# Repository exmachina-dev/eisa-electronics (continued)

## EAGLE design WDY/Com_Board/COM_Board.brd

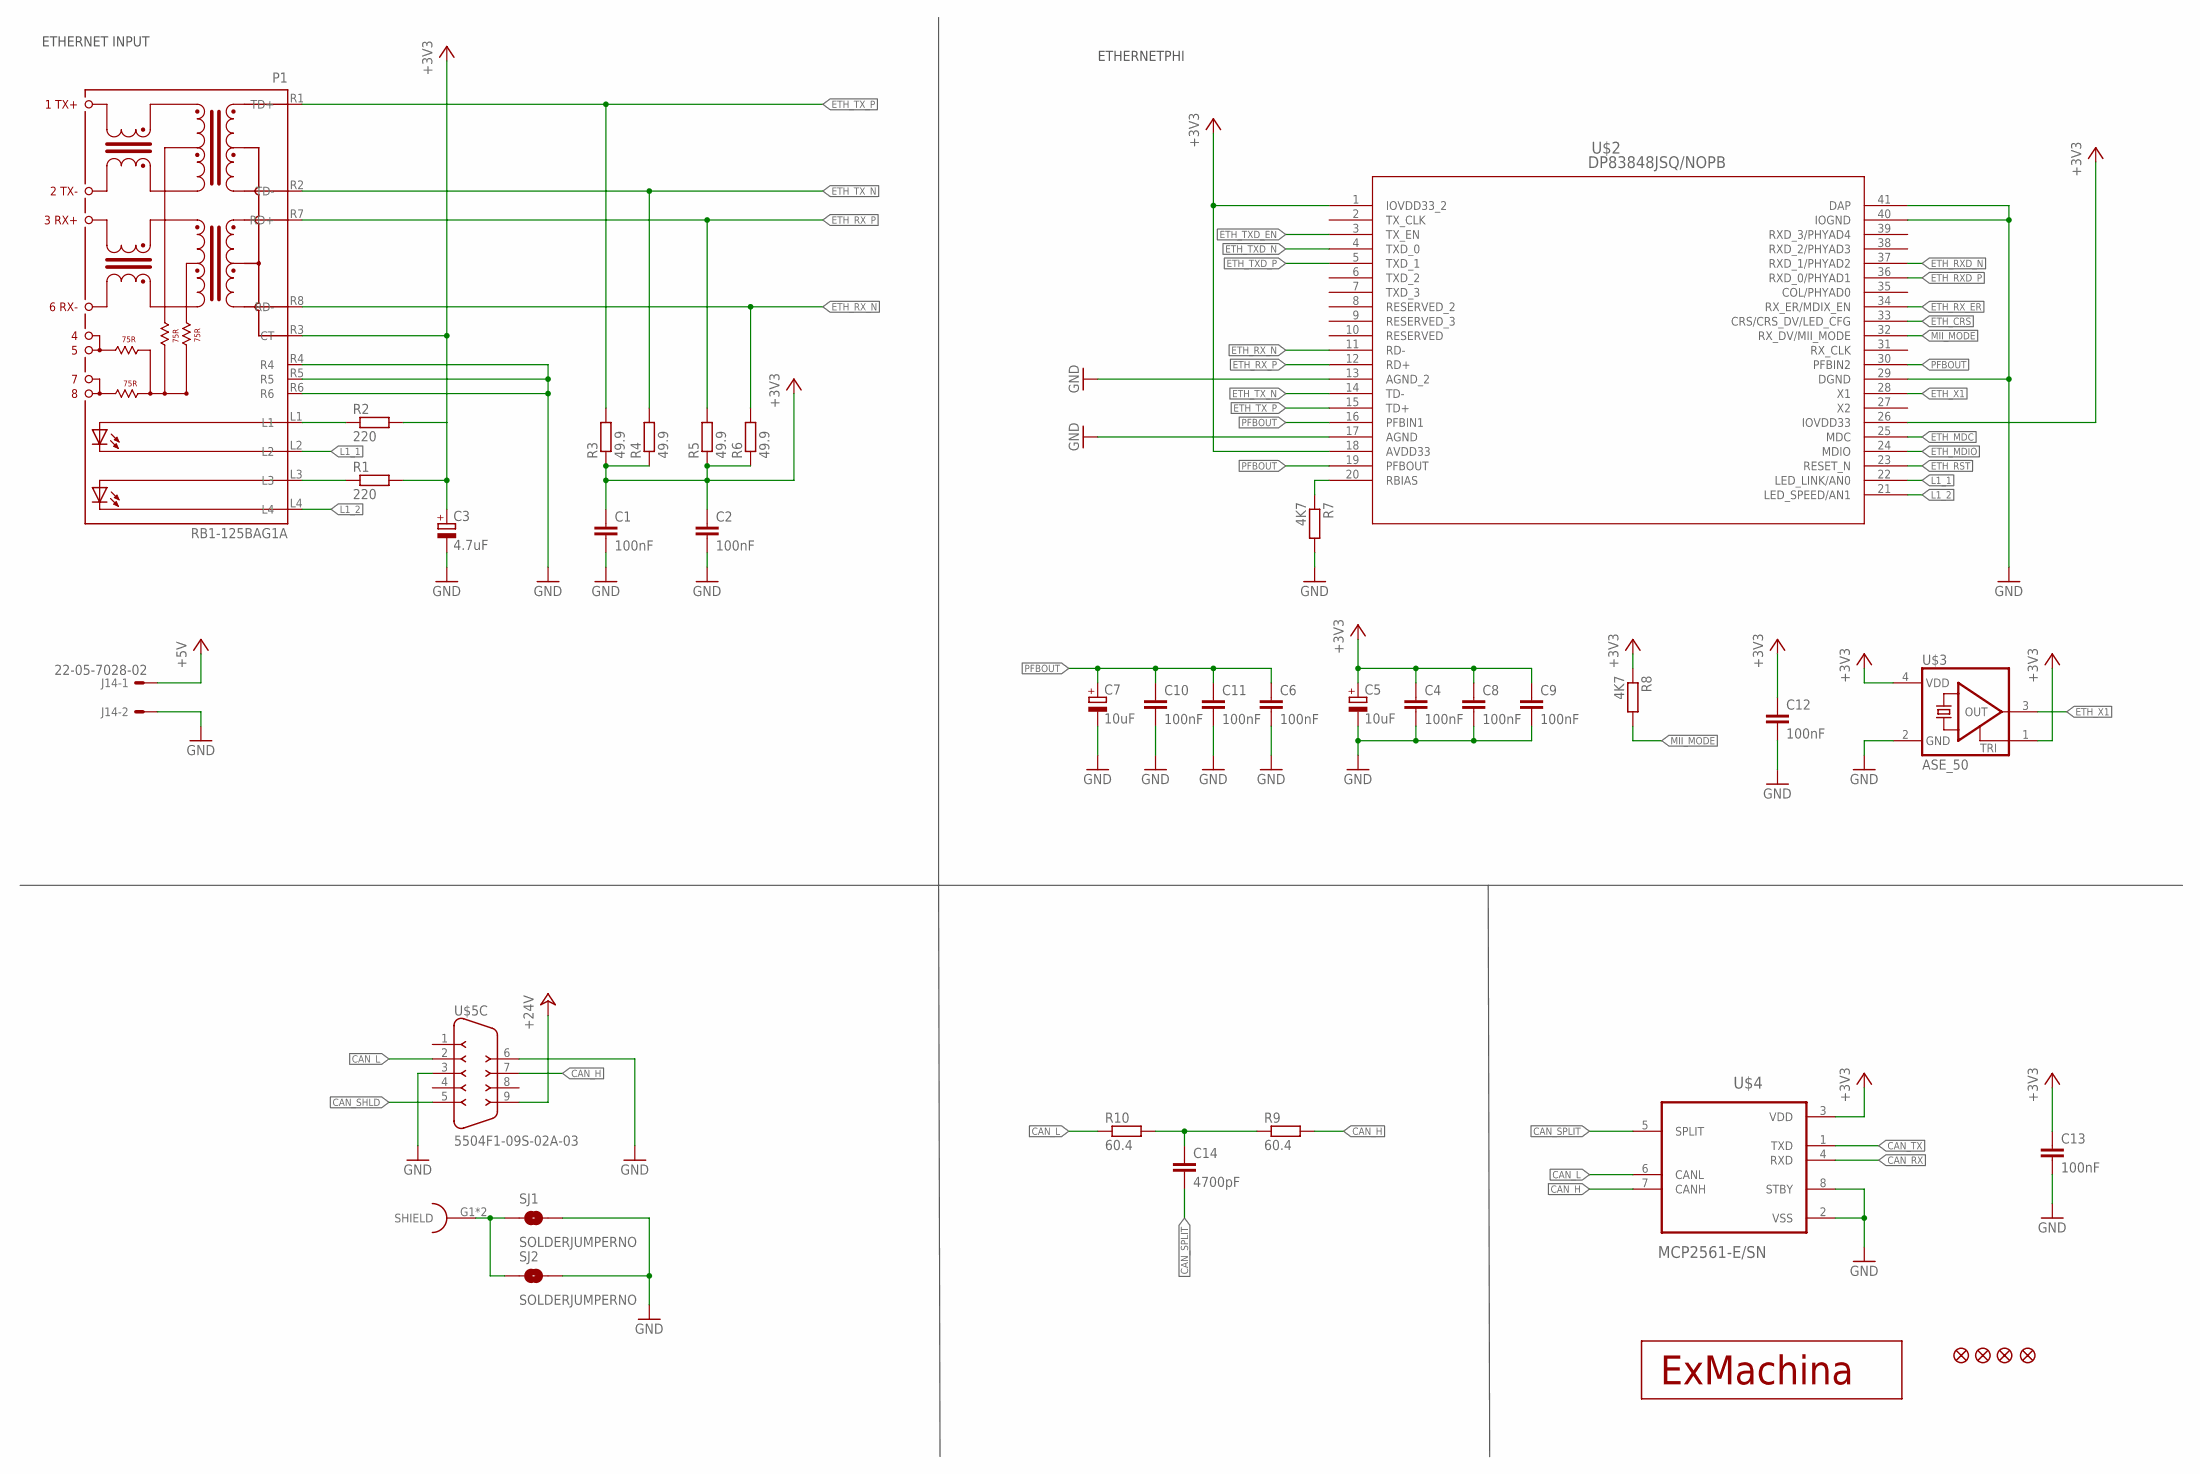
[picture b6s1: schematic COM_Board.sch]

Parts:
C1, C2, C4, C6, C8, C9, C10, C11, C12, C13: 100nF; C0603
C3: 4.7uF; CT3216
C5, C7: 10uF; CT3216
C14: 4700pF; C0603
J14: 22-05-7028-02; 7395-02
JP2, JP3, JP4, JP5: FIDUCIAL1X2; FIDUCIAL-1X2
P1: RB1-125BAG1A; WIZNET_RB1-125BAG1A
R1, R2: 220; R0603
R3, R4, R5, R6: 49.9; R0603
R7, R8: 4K7; R0603
R9, R10: 60.4; R0603
SJ1, SJ2: SOLDERJUMPERNO; SJ_2S-NO
U$1: EXMACHINA-LOGO-NAME; EXM-LOGO-BASELINE
U$2: DP83848JSQ/NOPB; SQA40B
U$3: ASE_50; ASE
U$4: MCP2561-E/SN; SOIC127P600X175-8N
U$5: 5504F1-09S-02A-03; 5504F1-09S-02A

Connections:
+3V3: C1.1, C2.1, C3.+, C4.1, C5.+, C8.1, C9.1, C12.1, C13.1, P1.R3 (CT), R1.2, R2.2, R3.1, R4.1, R5.1, R6.1, R8.1, U$2.1 (IOVDD33_2), U$2.18 (AVDD33), U$2.26 (IOVDD33), U$3.1 (TRI), U$3.4 (VDD), U$4.3 (VDD)
+5V: J14.1
+24V: U$5.9
CAN_H: R9.2, U$4.7 (CANH), U$5.7
CAN_L: R10.1, U$4.6 (CANL), U$5.2
CAN_RX: U$4.4 (RXD)
CAN_SHLD: U$5.5
CAN_SPLIT: C14.2, U$4.5 (SPLIT)
CAN_TX: U$4.1 (TXD)
ETH_CRS: U$2.33 (CRS/CRS_DV/LED_CFG)
ETH_MDC: U$2.25 (MDC)
ETH_MDIO: U$2.24 (MDIO)
ETH_RST: U$2.23 (RESET_N)
ETH_RXD_N: U$2.37 (RXD_1/PHYAD2)
ETH_RXD_P: U$2.36 (RXD_0/PHYAD1)
ETH_RX_ER: U$2.34 (RX_ER/MDIX_EN)
ETH_RX_N: P1.R8 (RD-), R6.2, U$2.11 (RD-)
ETH_RX_P: P1.R7 (RD+), R5.2, U$2.12 (RD+)
ETH_TXD_EN: U$2.3 (TX_EN)
ETH_TXD_N: U$2.4 (TXD_0)
ETH_TXD_P: U$2.5 (TXD_1)
ETH_TX_N: P1.R2 (TD-), R4.2, U$2.14 (TD-)
ETH_TX_P: P1.R1 (TD+), R3.2, U$2.15 (TD+)
ETH_X1: U$2.28 (X1), U$3.3 (OUT)
GND: C1.2, C2.2, C3.-, C4.2, C5.-, C6.2, C7.-, C8.2, C9.2, C10.2, C11.2, C12.2, C13.2, J14.2, P1.R4, P1.R5, P1.R6, R7.2, SJ1.2, SJ2.2, U$2.13 (AGND_2), U$2.17 (AGND), U$2.29 (DGND), U$2.40 (IOGND), U$2.41 (DAP), U$3.2 (GND), U$4.2 (VSS), U$4.8 (STBY), U$5.3, U$5.6
L1_1: P1.L2, U$2.22 (LED_LINK/AN0)
L1_2: P1.L4, U$2.21 (LED_SPEED/AN1)
MII_MODE: R8.2, U$2.32 (RX_DV/MII_MODE)
unnamed: C14.1, R9.1, R10.2
unnamed: R7.1, U$2.20 (RBIAS)
unnamed: SJ1.1, SJ2.1, U$5.G1 (SHIELD), U$5.G2 (SHIELD)
unnamed: P1.L1, R2.1
unnamed: P1.L3, R1.1
PFBOUT: C6.1, C7.+, C10.1, C11.1, U$2.16 (PFBIN1), U$2.19 (PFBOUT), U$2.30 (PFBIN2)

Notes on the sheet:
ETHERNET INPUT
ETHERNETPHI

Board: 2 copper layers, 37 parts (0 on the bottom side), 19 nets, no tracks yet.

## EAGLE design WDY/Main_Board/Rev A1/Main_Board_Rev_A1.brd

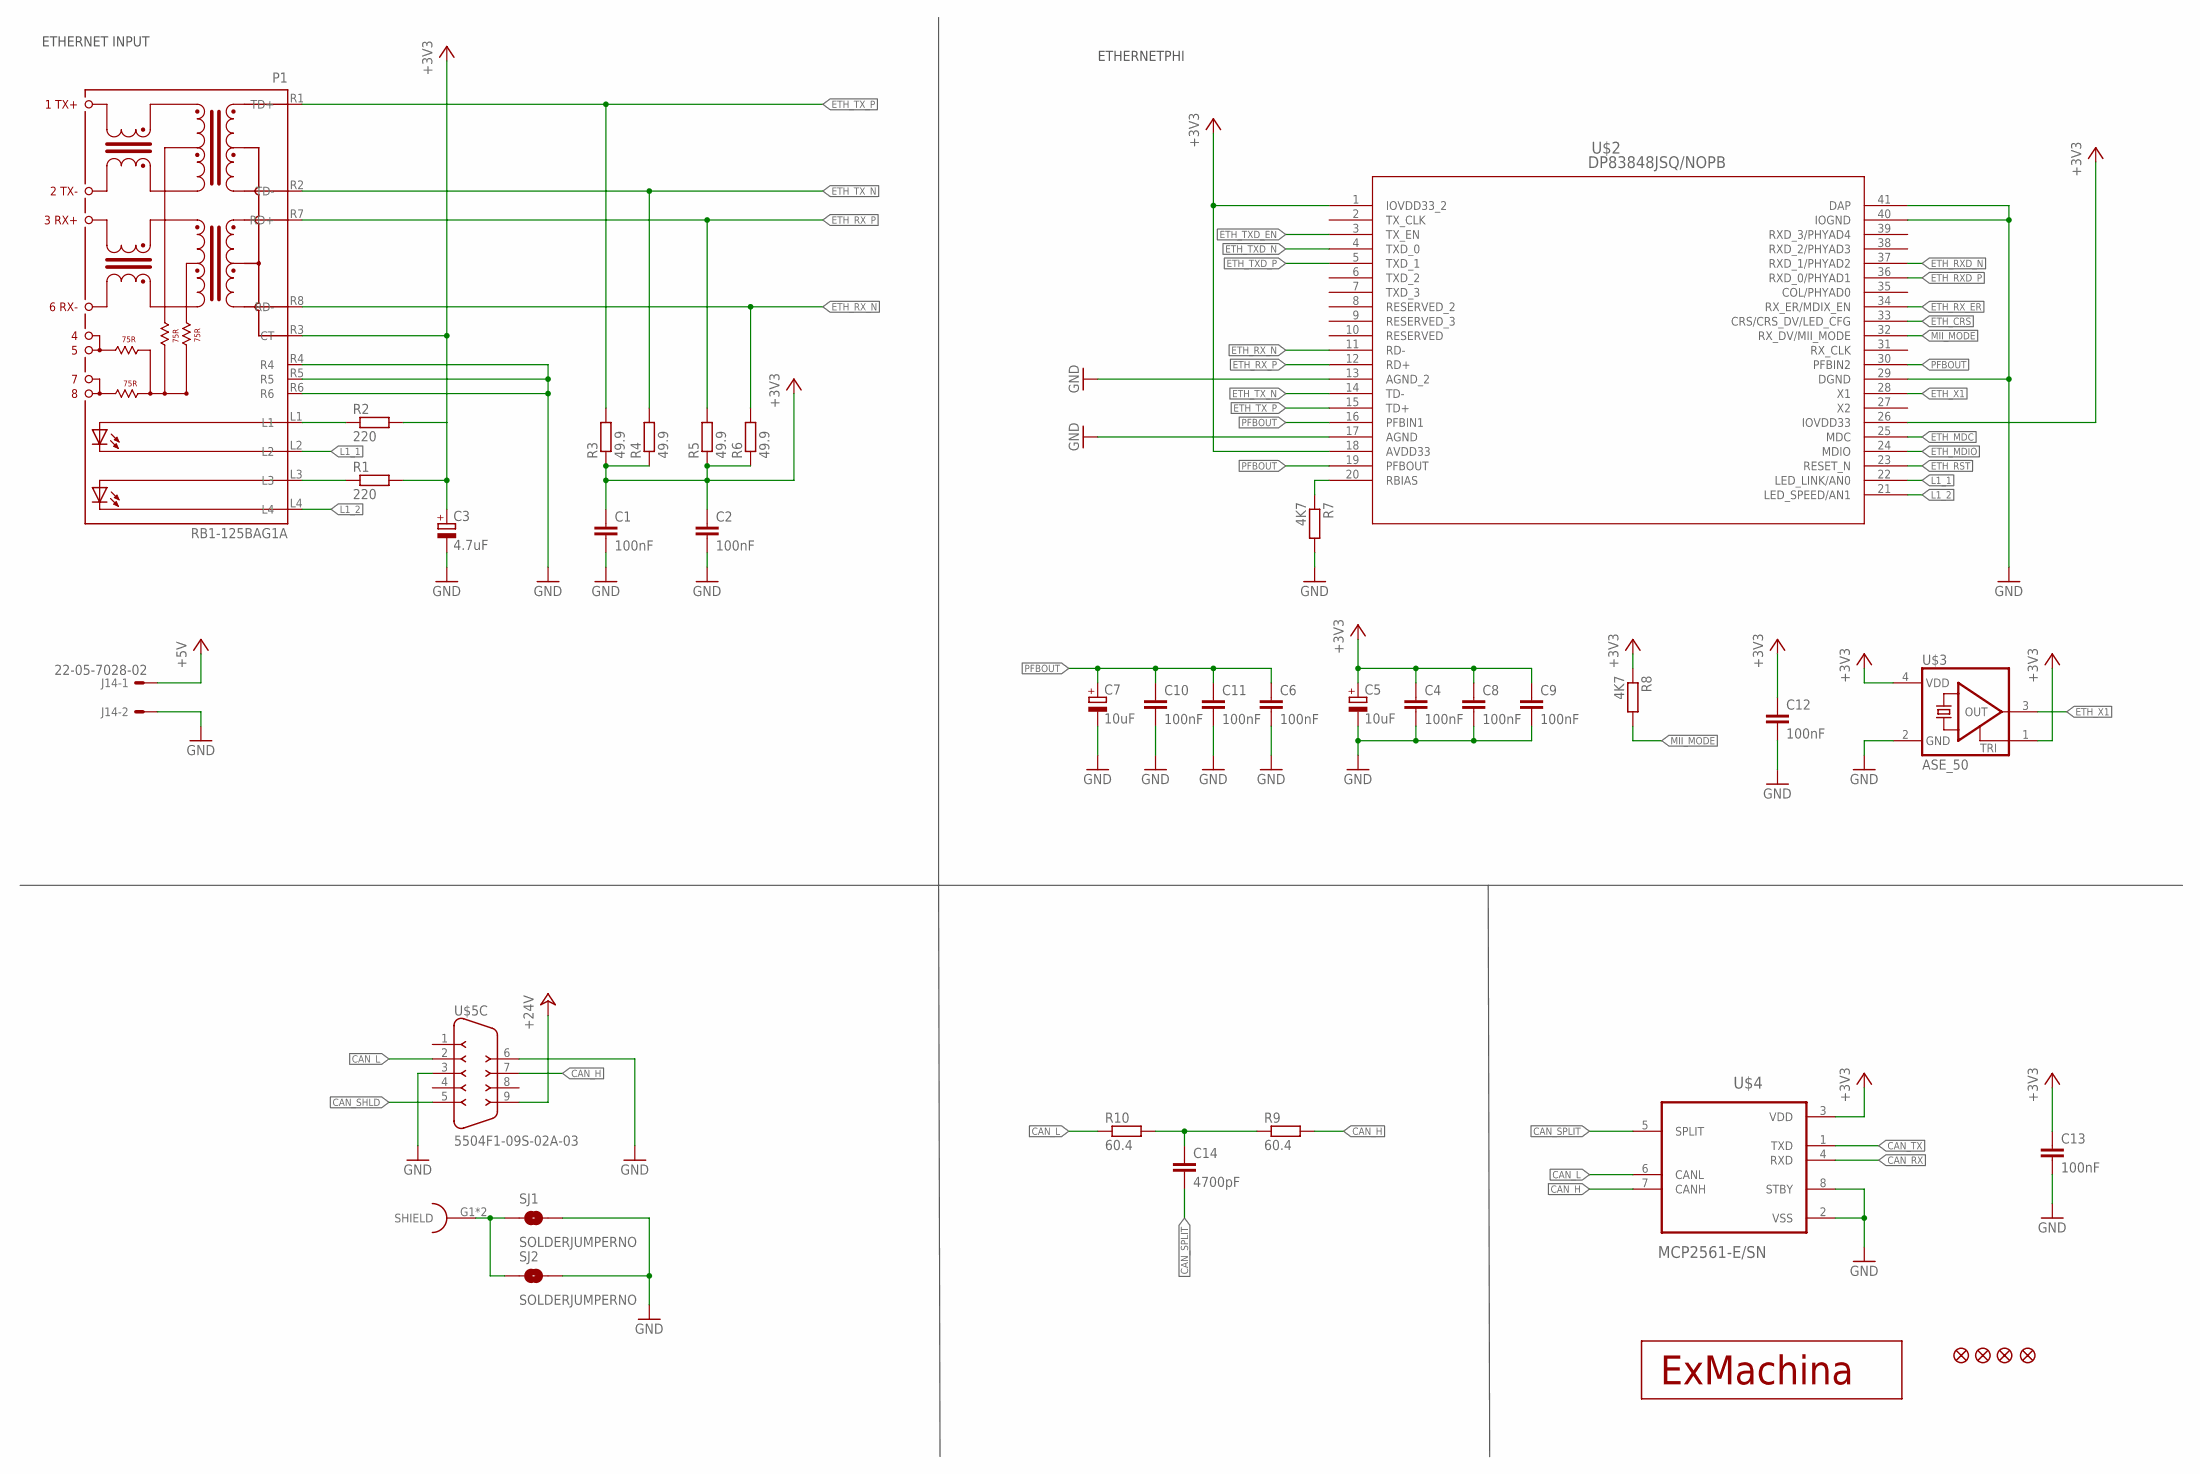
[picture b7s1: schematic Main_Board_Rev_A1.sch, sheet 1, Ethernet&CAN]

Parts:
C1, C2, C4, C6, C8, C9, C10, C11, C12, C13: 100nF; C0603
C3: 4.7uF; CT3216
C5, C7: 10uF; CT3216
C14: 4700pF; C0603
J14: 22-05-7028-02; 7395-02
JP2, JP3, JP4, JP5: FIDUCIAL1X2; FIDUCIAL-1X2
P1: RB1-125BAG1A; WIZNET_RB1-125BAG1A
R1, R2: 220; R0603
R3, R4, R5, R6: 49.9; R0603
R7, R8: 4K7; R0603
R9, R10: 60.4; R0603
SJ1, SJ2: SOLDERJUMPERNO; SJ_2S-NO
U$1: EXMACHINA-LOGO-NAME; EXM-LOGO-BASELINE
U$2: DP83848JSQ/NOPB; SQA40B
U$3: ASE_50; ASE
U$4: MCP2561-E/SN; SOIC127P600X175-8N
U$5: 5504F1-09S-02A-03; 5504F1-09S-02A

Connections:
+3V3: C1.1, C2.1, C3.+, C4.1, C5.+, C8.1, C9.1, C12.1, C13.1, P1.R3 (CT), R1.2, R2.2, R3.1, R4.1, R5.1, R6.1, R8.1, U$2.1 (IOVDD33_2), U$2.18 (AVDD33), U$2.26 (IOVDD33), U$3.1 (TRI), U$3.4 (VDD), U$4.3 (VDD); also elsewhere on the board
+5V: J14.1; also elsewhere on the board
+24V: U$5.9; also elsewhere on the board
CAN_H: R9.2, U$4.7 (CANH), U$5.7
CAN_L: R10.1, U$4.6 (CANL), U$5.2
CAN_RX: U$4.4 (RXD); also elsewhere on the board
CAN_SHLD: U$5.5
CAN_SPLIT: C14.2, U$4.5 (SPLIT)
CAN_TX: U$4.1 (TXD); also elsewhere on the board
ETH_CRS: U$2.33 (CRS/CRS_DV/LED_CFG); also elsewhere on the board
ETH_MDC: U$2.25 (MDC); also elsewhere on the board
ETH_MDIO: U$2.24 (MDIO); also elsewhere on the board
ETH_RST: U$2.23 (RESET_N)
ETH_RXD_N: U$2.37 (RXD_1/PHYAD2); also elsewhere on the board
ETH_RXD_P: U$2.36 (RXD_0/PHYAD1); also elsewhere on the board
ETH_RX_ER: U$2.34 (RX_ER/MDIX_EN); also elsewhere on the board
ETH_RX_N: P1.R8 (RD-), R6.2, U$2.11 (RD-)
ETH_RX_P: P1.R7 (RD+), R5.2, U$2.12 (RD+)
ETH_TXD_EN: U$2.3 (TX_EN); also elsewhere on the board
ETH_TXD_N: U$2.4 (TXD_0); also elsewhere on the board
ETH_TXD_P: U$2.5 (TXD_1); also elsewhere on the board
ETH_TX_N: P1.R2 (TD-), R4.2, U$2.14 (TD-)
ETH_TX_P: P1.R1 (TD+), R3.2, U$2.15 (TD+)
ETH_X1: U$2.28 (X1), U$3.3 (OUT)
GND: C1.2, C2.2, C3.-, C4.2, C5.-, C6.2, C7.-, C8.2, C9.2, C10.2, C11.2, C12.2, C13.2, J14.2, P1.R4, P1.R5, P1.R6, R7.2, SJ1.2, SJ2.2, U$2.13 (AGND_2), U$2.17 (AGND), U$2.29 (DGND), U$2.40 (IOGND), U$2.41 (DAP), U$3.2 (GND), U$4.2 (VSS), U$4.8 (STBY), U$5.3, U$5.6; also elsewhere on the board
L1_1: P1.L2, U$2.22 (LED_LINK/AN0)
L1_2: P1.L4, U$2.21 (LED_SPEED/AN1)
MII_MODE: R8.2, U$2.32 (RX_DV/MII_MODE)
unnamed: C14.1, R9.1, R10.2
unnamed: R7.1, U$2.20 (RBIAS)
unnamed: SJ1.1, SJ2.1, U$5.G1 (SHIELD), U$5.G2 (SHIELD)
unnamed: P1.L1, R2.1
unnamed: P1.L3, R1.1
PFBOUT: C6.1, C7.+, C10.1, C11.1, U$2.16 (PFBIN1), U$2.19 (PFBOUT), U$2.30 (PFBIN2)

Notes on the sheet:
ETHERNET INPUT
ETHERNETPHI

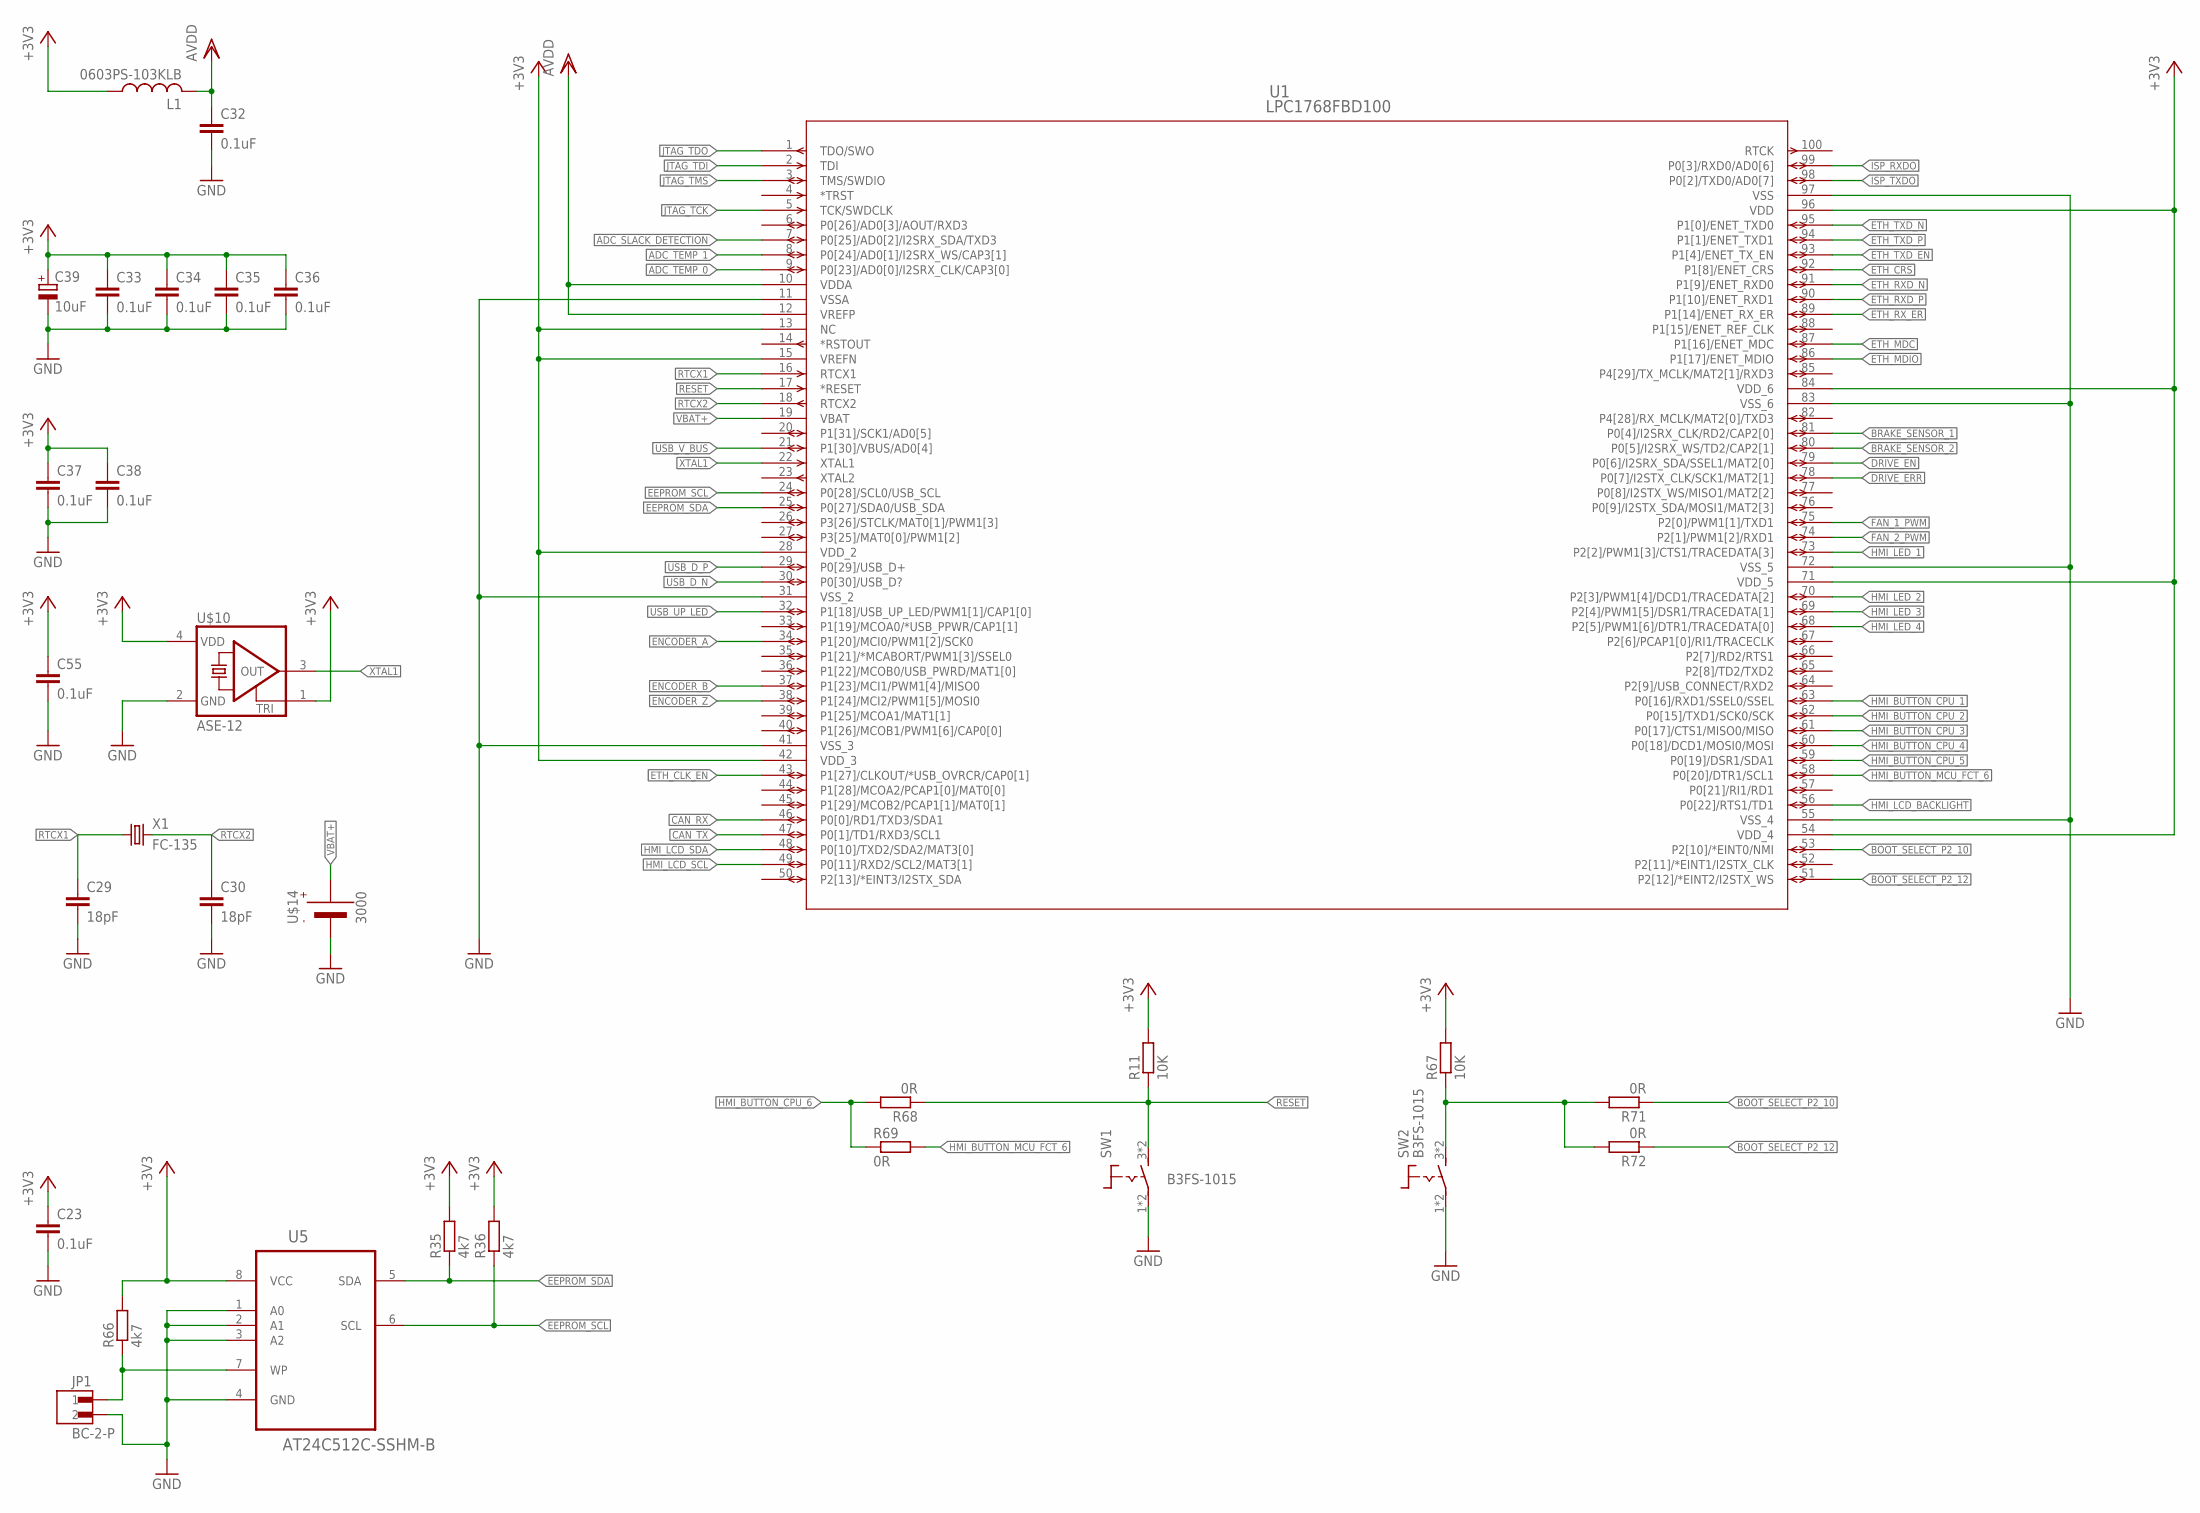
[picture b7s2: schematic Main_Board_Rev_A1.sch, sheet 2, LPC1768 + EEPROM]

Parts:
C23, C32, C33, C34, C35, C36, C37, C38, C55: 0.1uF; C0603
C29, C30: 18pF; C0603
C39: 10uF; CT3216
JP1: BC-2-P
L1: 0603PS-103KLB; 0603
R11, R67: 10K; R0603
R35, R36, R66: 4k7; R0603
R68, R69, R71, R72: 0R; R0603
SW1, SW2: B3FS-1015; B3FS
U1: LPC1768FBD100; SOT407-1
U5: AT24C512C-SSHM-B; SOIC127P600X175-8N
U$10: ASE-12; ASE
U$14: 3000
X1: FC-135

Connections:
+3V3: C23.1, C33.1, C34.1, C35.1, C36.1, C37.1, C38.1, C39.+, C55.1, L1.P$1 (1), R11.2, R35.2, R36.2, R66.2, R67.2, U1.13 (NC), U1.15 (VREFN), U1.28 (VDD_2), U1.42 (VDD_3), U1.54 (VDD_4), U1.71 (VDD_5), U1.84 (VDD_6), U1.96 (VDD), U5.8 (VCC), U$10.1 (TRI), U$10.4 (VDD); also elsewhere on the board
ADC_SLACK_DETECTION: U1.7 (P0[25]/AD0[2]/I2SRX_SDA/TXD3); also elsewhere on the board
ADC_TEMP_0: U1.9 (P0[23]/AD0[0]/I2SRX_CLK/CAP3[0]); also elsewhere on the board
ADC_TEMP_1: U1.8 (P0[24]/AD0[1]/I2SRX_WS/CAP3[1]); also elsewhere on the board
AVDD: C32.1, L1.P$2 (2), U1.10 (VDDA), U1.12 (VREFP); also elsewhere on the board
BOOT_SELECT_P2_10: R71.1, U1.53 (P2[10]/*EINT0/NMI)
BOOT_SELECT_P2_12: R72.1, U1.51 (P2[12]/*EINT2/I2STX_WS)
BRAKE_SENSOR_1: U1.81 (P0[4]/I2SRX_CLK/RD2/CAP2[0]); also elsewhere on the board
BRAKE_SENSOR_2: U1.80 (P0[5]/I2SRX_WS/TD2/CAP2[1]); also elsewhere on the board
CAN_RX: U1.46 (P0[0]/RD1/TXD3/SDA1); also elsewhere on the board
CAN_TX: U1.47 (P0[1]/TD1/RXD3/SCL1); also elsewhere on the board
DRIVE_EN: U1.79 (P0[6]/I2SRX_SDA/SSEL1/MAT2[0]); also elsewhere on the board
DRIVE_ERR: U1.78 (P0[7]/I2STX_CLK/SCK1/MAT2[1]); also elsewhere on the board
EEPROM_SCL: R36.1, U1.24 (P0[28]/SCL0/USB_SCL), U5.6 (SCL)
EEPROM_SDA: R35.1, U1.25 (P0[27]/SDA0/USB_SDA), U5.5 (SDA)
ENCODER_A: U1.34 (P1[20]/MCI0/PWM1[2]/SCK0); also elsewhere on the board
ENCODER_B: U1.37 (P1[23]/MCI1/PWM1[4]/MISO0); also elsewhere on the board
ENCODER_Z: U1.38 (P1[24]/MCI2/PWM1[5]/MOSI0); also elsewhere on the board
ETH_CLK_EN: U1.43 (P1[27]/CLKOUT/*USB_OVRCR/CAP0[1])
ETH_CRS: U1.92 (P1[8]/ENET_CRS); also elsewhere on the board
ETH_MDC: U1.87 (P1[16]/ENET_MDC); also elsewhere on the board
ETH_MDIO: U1.86 (P1[17]/ENET_MDIO); also elsewhere on the board
ETH_RXD_N: U1.91 (P1[9]/ENET_RXD0); also elsewhere on the board
ETH_RXD_P: U1.90 (P1[10]/ENET_RXD1); also elsewhere on the board
ETH_RX_ER: U1.89 (P1[14]/ENET_RX_ER); also elsewhere on the board
ETH_TXD_EN: U1.93 (P1[4]/ENET_TX_EN); also elsewhere on the board
ETH_TXD_N: U1.95 (P1[0]/ENET_TXD0); also elsewhere on the board
ETH_TXD_P: U1.94 (P1[1]/ENET_TXD1); also elsewhere on the board
FAN_1_PWM: U1.75 (P2[0]/PWM1[1]/TXD1); also elsewhere on the board
FAN_2_PWM: U1.74 (P2[1]/PWM1[2]/RXD1); also elsewhere on the board
GND: C23.2, C29.2, C30.2, C32.2, C33.2, C34.2, C35.2, C36.2, C37.2, C38.2, C39.-, C55.2, JP1.2, SW1.1 (2), SW1.2, SW2.1 (2), SW2.2, U1.11 (VSSA), U1.31 (VSS_2), U1.41 (VSS_3), U1.55 (VSS_4), U1.72 (VSS_5), U1.83 (VSS_6), U1.97 (VSS), U5.1 (A0), U5.2 (A1), U5.3 (A2), U5.4 (GND), U$10.2 (GND), U$14.- (VBAT-); also elsewhere on the board
HMI_BUTTON_CPU_1: U1.63 (P0[16]/RXD1/SSEL0/SSEL); also elsewhere on the board
HMI_BUTTON_CPU_2: U1.62 (P0[15]/TXD1/SCK0/SCK); also elsewhere on the board
HMI_BUTTON_CPU_3: U1.61 (P0[17]/CTS1/MISO0/MISO); also elsewhere on the board
HMI_BUTTON_CPU_4: U1.60 (P0[18]/DCD1/MOSI0/MOSI); also elsewhere on the board
HMI_BUTTON_CPU_5: U1.59 (P0[19]/DSR1/SDA1); also elsewhere on the board
HMI_BUTTON_CPU_6: R68.2, R69.1; also elsewhere on the board
HMI_BUTTON_MCU_FCT_6: R69.2, U1.58 (P0[20]/DTR1/SCL1)
HMI_LCD_BACKLIGHT: U1.56 (P0[22]/RTS1/TD1); also elsewhere on the board
HMI_LCD_SCL: U1.49 (P0[11]/RXD2/SCL2/MAT3[1]); also elsewhere on the board
HMI_LCD_SDA: U1.48 (P0[10]/TXD2/SDA2/MAT3[0]); also elsewhere on the board
HMI_LED_1: U1.73 (P2[2]/PWM1[3]/CTS1/TRACEDATA[3]); also elsewhere on the board
HMI_LED_2: U1.70 (P2[3]/PWM1[4]/DCD1/TRACEDATA[2]); also elsewhere on the board
HMI_LED_3: U1.69 (P2[4]/PWM1[5]/DSR1/TRACEDATA[1]); also elsewhere on the board
HMI_LED_4: U1.68 (P2[5]/PWM1[6]/DTR1/TRACEDATA[0]); also elsewhere on the board
ISP_RXDO: U1.99 (P0[3]/RXD0/AD0[6]); also elsewhere on the board
ISP_TXDO: U1.98 (P0[2]/TXD0/AD0[7]); also elsewhere on the board
JTAG_TCK: U1.5 (TCK/SWDCLK); also elsewhere on the board
JTAG_TDI: U1.2 (TDI); also elsewhere on the board
JTAG_TDO: U1.1 (TDO/SWO); also elsewhere on the board
JTAG_TMS: U1.3 (TMS/SWDIO); also elsewhere on the board
unnamed: R67.1, R71.2, R72.2, SW2.3 (1), SW2.4 (1)
unnamed: JP1.1, R66.1, U5.7 (WP)
RESET: R11.1, R68.1, SW1.3 (1), SW1.4 (1), U1.17 (*RESET); also elsewhere on the board
RTCX1: C29.1, U1.16 (RTCX1), X1.1
RTCX2: C30.1, U1.18 (RTCX2), X1.2
USB_D_N: U1.30 (P0[30]/USB_D?); also elsewhere on the board
USB_D_P: U1.29 (P0[29]/USB_D+); also elsewhere on the board
USB_UP_LED: U1.32 (P1[18]/USB_UP_LED/PWM1[1]/CAP1[0]); also elsewhere on the board
USB_V_BUS: U1.21 (P1[30]/VBUS/AD0[4]); also elsewhere on the board
VBAT+: U1.19 (VBAT), U$14.+1 (VBAT+), U$14.+2 (VBAT+)
XTAL1: U1.22 (XTAL1), U$10.3 (OUT)

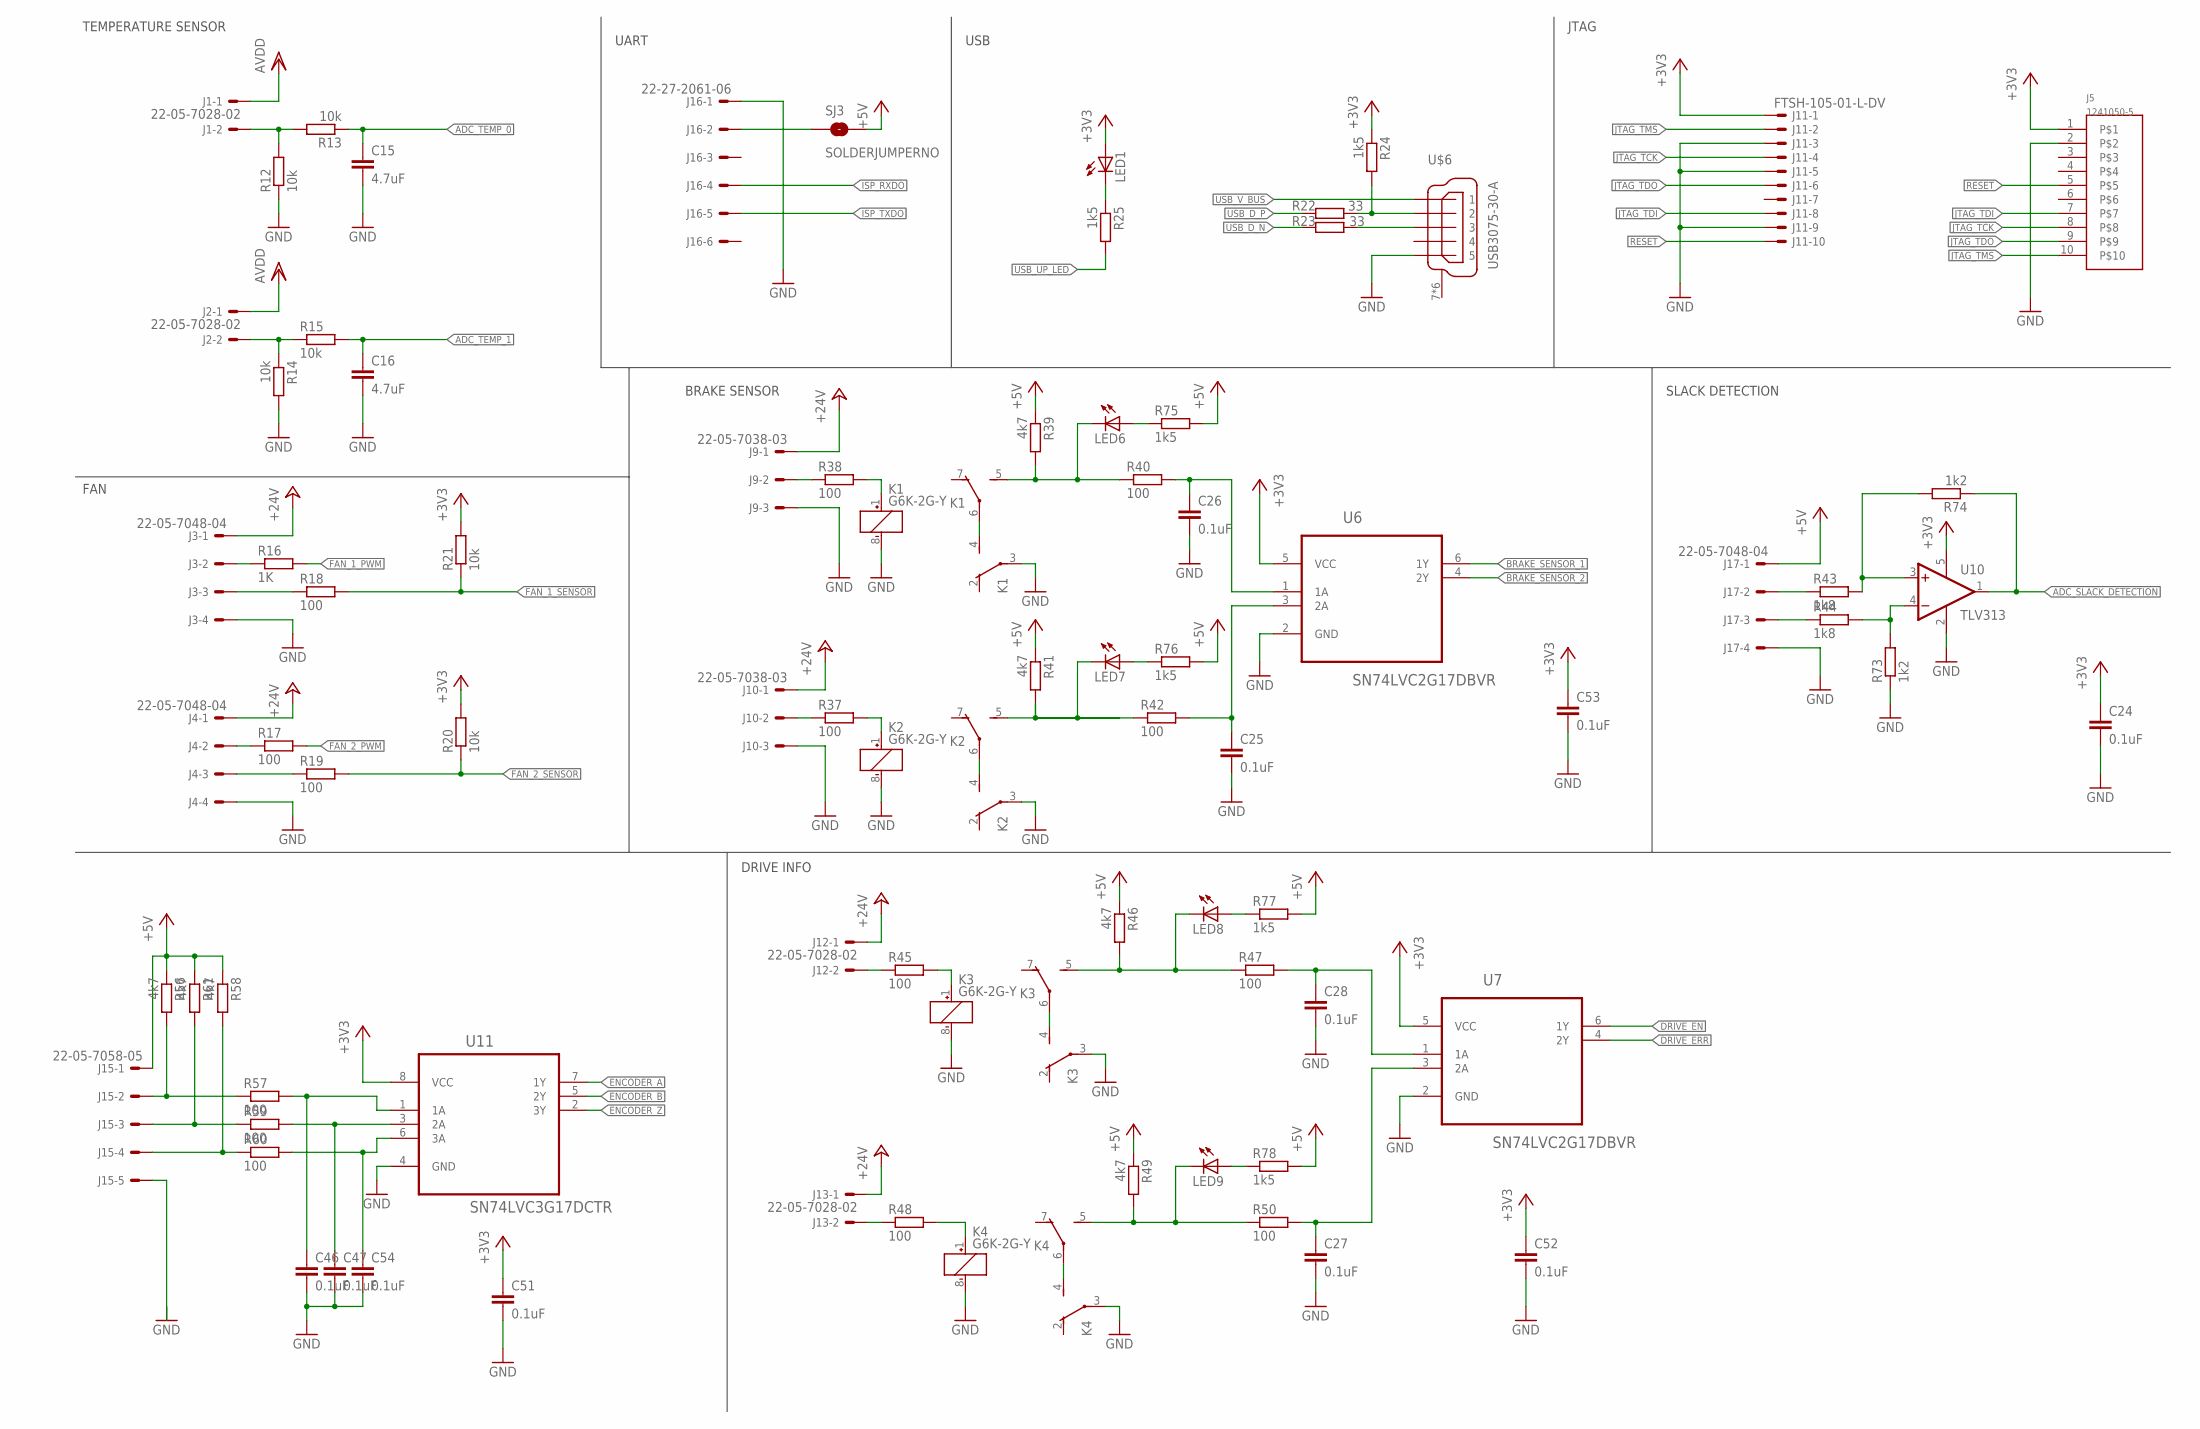
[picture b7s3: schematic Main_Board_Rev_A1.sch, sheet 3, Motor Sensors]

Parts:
C15, C16: 4.7uF; C0603
C24, C25, C26, C27, C28, C46, C47, C51, C52, C53, C54: 0.1uF; C0603
J1, J2, J12, J13: 22-05-7028-02; 7395-02
J3, J4, J17: 22-05-7048-04; 7395-04
J5: 1241050-5; 2.54/2X5
J9, J10: 22-05-7038-03; 7395-03
J11: FTSH-105-01-L-DV
J15: 22-05-7058-05; 7395-05
J16: 22-27-2061-06; 6410-06
K1, K2, K3, K4: G6K-2G-Y
LED1, LED6, LED7, LED8, LED9: LEDCHIPLED_0603; CHIPLED_0603
R12, R13, R14, R15, R20, R21: 10k; R0603
R16: 1K; R0603
R17, R18, R19, R37, R38, R40, R42, R45, R47, R48, R50, R57, R59, R60: 100; R0603
R22, R23: 33; R0603
R24, R25, R75, R76, R77, R78: 1k5; R0603
R39, R41, R46, R49, R56, R58, R61: 4k7; R0603
R43, R44: 1k8; R0603
R73, R74: 1k2; R0603
SJ3: SOLDERJUMPERNO; SJ_2S-NO
U6, U7: SN74LVC2G17DBVR; SOT95P280X145-6N
U10: TLV313; SOT23-DBV
U11: SN74LVC3G17DCTR; SOP65P400X130-8N
U$6: USB3075-30-A; USB_MICROB_SMT

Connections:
+3V3: C24.1, C51.1, C52.1, C53.1, J5.1, J11.1, LED1.A, R20.2, R21.2, R24.1, U6.5 (VCC), U7.5 (VCC), U10.5 (V+), U11.8 (VCC); also elsewhere on the board
+5V: J15.1, J17.1, R39.1, R41.1, R46.1, R49.1, R56.1, R58.1, R61.1, R75.2, R76.2, R77.2, R78.2, SJ3.2; also elsewhere on the board
+24V: J3.1, J4.1, J9.1, J10.1, J12.1, J13.1; also elsewhere on the board
ADC_SLACK_DETECTION: R74.1, U10.1 (OUT); also elsewhere on the board
ADC_TEMP_0: C15.1, R13.1; also elsewhere on the board
ADC_TEMP_1: C16.1, R15.2; also elsewhere on the board
AVDD: J1.1, J2.1; also elsewhere on the board
BRAKE_SENSOR_1: U6.6 (1Y); also elsewhere on the board
BRAKE_SENSOR_2: U6.4 (2Y); also elsewhere on the board
DRIVE_EN: U7.6 (1Y); also elsewhere on the board
DRIVE_ERR: U7.4 (2Y); also elsewhere on the board
ENCODER_A: U11.7 (1Y); also elsewhere on the board
ENCODER_B: U11.5 (2Y); also elsewhere on the board
ENCODER_Z: U11.2 (3Y); also elsewhere on the board
FAN_1_PWM: R16.2; also elsewhere on the board
FAN_1_SENSOR: R18.2, R21.1
FAN_2_PWM: R17.2; also elsewhere on the board
FAN_2_SENSOR: R19.2, R20.1
GND: C15.2, C16.2, C24.2, C25.2, C26.2, C27.2, C28.2, C46.2, C47.2, C51.2, C52.2, C53.2, C54.2, J3.4, J4.4, J5.2, J9.3, J10.3, J11.3, J11.5, J11.9, J16.1, J17.4, K1.3, K1.8 (-), K2.3, K2.8 (-), K3.3, K3.8 (-), K4.3, K4.8 (-), R12.1, R14.2, R73.1, U6.2 (GND), U7.2 (GND), U10.2 (V-), U11.4 (GND), U$6.5; also elsewhere on the board
ISP_RXDO: J16.4; also elsewhere on the board
ISP_TXDO: J16.5; also elsewhere on the board
JTAG_TCK: J5.8, J11.4; also elsewhere on the board
JTAG_TDI: J5.7, J11.8; also elsewhere on the board
JTAG_TDO: J5.9, J11.6; also elsewhere on the board
JTAG_TMS: J5.10, J11.2; also elsewhere on the board
unnamed: J3.2, R16.1
unnamed: J4.3, R19.1
unnamed: J4.2, R17.1
unnamed: J3.3, R18.1
unnamed: R22.1, R24.2, U$6.2
unnamed: R23.1, U$6.3
unnamed: LED1.C, R25.1
unnamed: J9.2, R38.1
unnamed: J10.2, R37.1
unnamed: K1.1 (+), R38.2
unnamed: K3.1 (+), R45.2
unnamed: K1.4 (S), K1.6
unnamed: J17.2, R43.1
unnamed: J12.2, R45.1
unnamed: K4.1 (+), R48.2
unnamed: J15.2, R56.2, R57.1
unnamed: J13.2, R48.1
unnamed: C25.1, R42.2, U6.3 (2A)
unnamed: C26.1, R40.2, U6.1 (1A)
unnamed: J15.3, R59.1, R61.2
unnamed: C28.1, R47.2, U7.1 (1A)
unnamed: C27.1, R50.2, U7.3 (2A)
unnamed: J15.4, R58.2, R60.1
unnamed: C54.1, R60.2, U11.6 (3A)
unnamed: C47.1, R59.2, U11.3 (2A)
unnamed: C46.1, R57.2, U11.1 (1A)
unnamed: K2.1 (+), R37.2
unnamed: K2.4 (S), K2.6
unnamed: K1.5 (S), LED6.C, R39.2, R40.1
unnamed: K4.4 (S), K4.6
unnamed: K3.4 (S), K3.6
unnamed: R43.2, R74.2, U10.3 (+IN)
unnamed: J1.2, R12.2, R13.2
unnamed: J2.2, R14.1, R15.1
unnamed: R44.2, R73.2, U10.4 (-IN)
unnamed: J17.3, R44.1
unnamed: J16.2, SJ3.1
unnamed: LED6.A, R75.1
unnamed: K2.5 (S), LED7.C, R41.2, R42.1
unnamed: LED7.A, R76.1
unnamed: K3.5 (S), LED8.C, R46.2, R47.1
unnamed: LED8.A, R77.1
unnamed: K4.5 (S), LED9.C, R49.2, R50.1
unnamed: LED9.A, R78.1
RESET: J5.5, J11.10; also elsewhere on the board
USB_D_N: R23.2; also elsewhere on the board
USB_D_P: R22.2; also elsewhere on the board
USB_UP_LED: R25.2; also elsewhere on the board
USB_V_BUS: U$6.1; also elsewhere on the board

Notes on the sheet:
USB
JTAG
TEMPERATURE SENSOR
FAN
SLACK DETECTION
BRAKE SENSOR
DRIVE INFO
UART
